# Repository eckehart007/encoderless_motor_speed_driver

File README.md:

# encoderless_motor_speed_driver

Current sense amplifier:
http://www.ti.com/tool/INA381EVM

https://eu.mouser.com/ProductDetail/Texas-Instruments/INA381A2IDSGR?qs=sGAEpiMZZMvEn2pkGav3bMtYv3jXcK%2fsQAFbDzm4iklEVnUVdeI9%2fg%3d%3d

Motor driver:
https://www.ebay.com/itm/Arduino-DRV8871-H-Bridge-DC-Motor-Driver-Breakout-Board-PWM-Control-Module-3-6A/311843855031?_trkparms=aid%3D111001%26algo%3DREC.SEED%26ao%3D1%26asc%3D20160727114228%26meid%3D033989c939c24d93b7b54e77079282a2%26pid%3D100290%26rk%3D1%26rkt%3D1%26mehot%3Dag%26sd%3D311843855031%26itm%3D311843855031&_trksid=p2060778.c100290.m3507

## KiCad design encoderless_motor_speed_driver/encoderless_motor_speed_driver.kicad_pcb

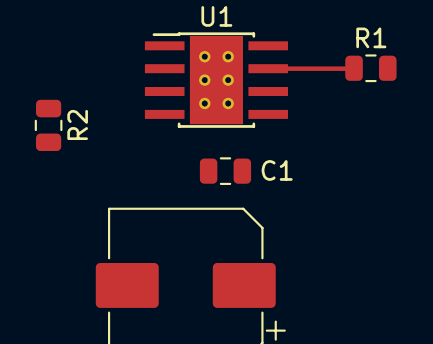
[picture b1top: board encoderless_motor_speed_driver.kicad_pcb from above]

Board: 2 copper layers, 5 parts (0 on the bottom side), 4 nets.

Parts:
C1: C; C_0805_2012Metric
C2: CP; CP_Elec_8x10
R1: MeanShunt; R_0805_2012Metric
R2: 30kR; R_0805_2012Metric
U1: DRV8871DDA; Texas_HTSOP-8-1EP_3.9x4.9mm_P1.27mm_EP2.95x4.9mm_Mask2.4x3.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

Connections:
GND: C1.2, C2.2, R1.2, R2.2, U1.1, U1.9
unnamed: R1.1, U1.7
unnamed: R2.1, U1.4
VCC: C1.1, C2.1, U1.5

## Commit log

2020-01-05 Started schemtatic
